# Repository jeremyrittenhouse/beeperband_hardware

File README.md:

This is the JITX-enabled beeper band design. 

The beeper design was started from a schematic but reworked using the JITX platform with the following features:
1) part discovery and bom generation
2) pin assignment for optimal connections between MCU and peripherals
3) adaptive, length-matched and differential trace implementation
4) semi-automatic power plane generation via voronoi region expansion

Note: to use the JITX platform, you will need to contact JITX for access to a beta version which enables some of the advanced features. (this note will go away when those features are in GA)

To run the code, open this repo in VSCode (w/JITX enabled) and load the file main.stanza. 
Press "Ctrl" + "Enter" in the file to run it. 

Please let me know if you have any questions. b.gupta@jitx.com

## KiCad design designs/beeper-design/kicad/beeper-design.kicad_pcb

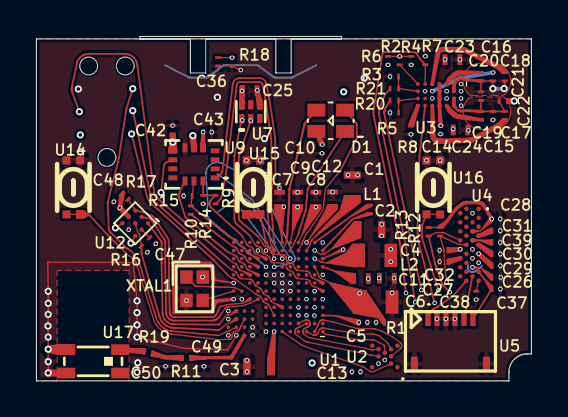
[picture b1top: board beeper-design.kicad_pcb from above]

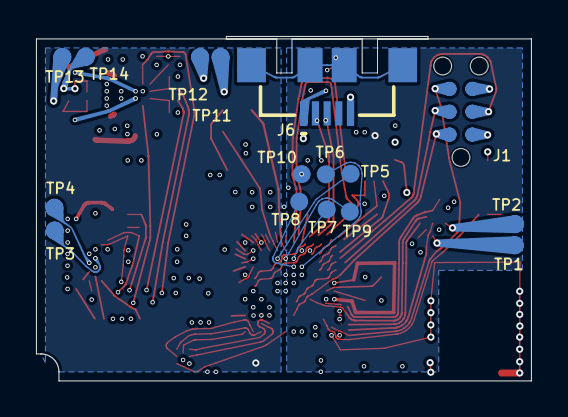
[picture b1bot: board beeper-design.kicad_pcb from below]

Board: 4 copper layers, 27.5 x 19.0 mm, 95 parts (16 on the bottom side), 87 nets.

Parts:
C1: 22u; Pkg0603_1
C2: 22u; Pkg0603_2
C3: 22u; Pkg0603
C4: 47u; Pkg0805
C5: 100n; Pkg0201_29
C6: 47u; Pkg0805_1
C7: 10u; Pkg0402_2
C8: 10u; Pkg0402_4
C9: 10u; Pkg0402_6
C10: 2.2u; Pkg0201_38
C11: 10u; Pkg0402_7
C12: 10u; Pkg0402
C13: 1u; Pkg0201
C14: 2.2u; Pkg0201_45
C15: 470n; Pkg0201_42
C16: 470n; Pkg0201_4
C17: 22n; Pkg0201_18
C18: 22n; Pkg0201_30
C19: 10n; Pkg0201_41
C20: 10n; Pkg0201_3
C21: 270p; Pkg0201_16
C22: 10n; Pkg0201_28
C23: 10u; Pkg0402_8
C24: 4.7u; Pkg0402_1
C25: 4.7u; Pkg0402_3
C26: 1u; Pkg0201_7
C27: 100n; Pkg0201_24
C28: 1u; Pkg0201_12
C29: 1u; Pkg0201_46
C30: 1u; Pkg0201_33
C31: 1u; Pkg0201_43
C32: 1u; Pkg0201_35
C36: 100n; Pkg0201_2
C37: 1u; Pkg0201_10
C38: 1u; Pkg0201_21
C39: 1u; Pkg0201_20
C42: 100n; Pkg0201_14
C43: 100n; Pkg0201_26
C47: 1u; Pkg0201_27
C48: 1u; Pkg0201_37
C49: 1p; Pkg0201_13
C50: 1p; Pkg0201_32
D1: LP_4
J1: TC2030_IDC_NL_FOOTPRINT
J6: GCT_USB3100_XX_X_REVB_1
L1: 470n; Pkg0201_11
L2: 1u; Pkg0402_5
R1: 0R; Pkg0201_47
R2: 845R; Pkg0201_9
R3: 10K; Pkg0201_6
R4: 20K; Pkg0201_34
R5: 10K; Pkg0201_44
R6: 196R; Pkg0201_23
R7: 10K; Pkg0201_19
R8: 1K; Pkg0201_31
R9: 0R; Pkg0201_8
R10: 0R; Pkg0201_17
R11: 0R; Pkg0201_22
R12, R13: 8K2; Pkg0201_1
R14, R15: 8K2; Pkg0201_36
R16, R17: 8K2; Pkg0201_5
R18: 100K; Pkg0201_40
R19: 0R; Pkg0201_39
R20: 0R; Pkg0201_15
R21: 0R; Pkg0201_25
TP1, TP2, TP3, TP4, TP5, TP6, TP7, TP8, TP9, TP10, TP11, TP12, TP13, TP14: SMD_TESTPT
U1: LP_7
U2: WLCSP_12
U3: LP_5
U4: LP_2
U5: LP_3
U7: SON_6_L1_5_W1_0_P0_50_BL
U9: LP
U12: LP_6
U14, U15, U16: LP_1
U17: Pkg_2450AT18D0100_STD_R_1
XTAL1: CRYSTAL_SMD_4P_L2_0_W1_6_BL_1

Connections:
AC1: C15.1, C17.1, C19.1, C21.2, C22.2, U3.B3, U3.B4
AC2: C16.1, C18.1, C20.1, C21.1, TP14.p, U3.B1, U3.B2
AD: R8.1, U3.G4
BOOT1: C19.2, U3.C4
BOOT2: C20.2, U3.C1
CLAMP1: C15.2, U3.E3
CLAMP2: C16.2, U3.E2
COMM1: C17.2, U3.E4
COMM2: C18.2, U3.E1
D+: J6.3, U1.F1, U7.1
D-: J6.2, U1.G1, U7.2
DACREF: C31.2, U4.A7
EN1: R5.1, R20.1, U3.G3
EN2: R3.1, R21.1, U3.G2
FOD: R2.2, R4.1, R6.1, U3.F2
GND: C1.1, C2.1, C3.1, C4.1, C5.1, C6.1, C7.1, C8.1, C9.1, C10.1, C11.1, C12.1, C13.1, C14.1, C23.1, C24.1, C25.1, C26.1, C27.1, C28.1, C29.1, C30.1, C31.1, C32.1, C36.2, C37.1, C38.1, C39.1, C42.1, C43.1, C47.1, C48.1, C49.2, C50.2, J1.5, J6.5, R3.2, R5.2, R6.2, R7.2, R8.2, R18.2, TP10.p, TP12.p, U1.A8, U1.A9, U1.A11, U1.A12, U1.B9, U1.C2, U1.C12, U1.D12, U1.E11, U1.E12, U1.F5, U1.F6, U1.G5, U1.G6, U1.G7, U1.G12, U1.H1, U1.H6, U1.H7, U1.H8, U1.L8, U1.L9, U1.M1, U2.C3, U3.A1, U3.A2, U3.A3, U3.A4, U4.B2, U4.B10, U5.2, U5.3, U5.4, U5.7, U5.8, U7.4, U9.7, U12.B3, U14.B, U14.B1, U15.B, U15.B1, U16.B, U16.B1, U17.2, U17.3, U17.4, XTAL1.2, XTAL1.4
ILIM: R2.1, U3.G1
LX: L1.1, U1.M2
LY: L1.2, U1.L1
LZ: L2.1, U1.J1
MICBIAS1: C37.2, U4.A15, U5.6
MICBIAS2: C38.2, U4.A17
OUT+: TP1.p, U12.A3
OUT-: TP2.p, U12.C3
RECT: C23.2, C24.2, R4.2, U3.C2, U3.C3
REG: C47.2, U12.A2
RF1: C49.1, R11.1, U1.A10
RF2: C50.1, R11.2, R19.1
RF3: R19.2, U17.1
SHIELD: C36.1, J6.6, J6.7, J6.8, J6.9, R18.1
SP_N: TP4.p, U4.A13
SP_P: TP3.p, U4.B12
V12: C1.2, U1.L3
V14RF: C2.2, C3.2, U1.A7, U1.L2
V18F: C5.2, C13.2, R1.1, U1.C1, U2.B2
VBAT: C8.2, TP11.p, U1.M4
VBUS: C9.2, C14.2, C25.2, J1.1, J6.1, U1.M5, U3.D1, U3.D2, U3.D3, U3.D4, U7.6
VDD1P8: C4.2, C42.2, C43.2, R14.2, R15.2, U1.K2, U9.5, U9.8
VDD1P8P: C6.2, C28.2, R1.2, R12.2, R13.2, U1.J2, U4.B6
VDD3P0: C7.2, C26.2, C32.2, U1.M6, U4.B14, U4.D10
VDDSYS: C11.2, C12.2, C29.2, C48.2, L2.2, R16.2, R17.2, U1.M3, U4.A11, U12.C2
VDIG: C27.2, U4.D12
VLED: C10.2, D1.2, U1.K1
VMID: C30.2, U4.A9
VREF: C39.2, U4.B8
XTAL32Mm: U1.F12, XTAL1.3
XTAL32Mp: U1.F11, XTAL1.1
board-io_rgb_b: D1.4, U1.L4
board-io_rgb_g: D1.3, U1.L6
board-io_rgb_r: D1.1, U1.L5
cap_p1: C22.1, TP13.p
codec-i2c-net_scl: R13.1, U1.C3, U4.D8
codec-i2c-net_sda: R12.1, U1.D4, U4.C9
codec-pdm-net_clk: U4.C17, U5.1
codec-pdm-net_data: U4.B16, U5.5
mcu_conn-uart_rx: J1.3, U1.H10
mcu_conn-uart_tx: J1.6, U1.B11
mcu_dbg-m33_swdio: J1.2, U1.C7
mcu_hap-gpio0_gpio: U1.D11, U12.A1
mcu_hap-gpio1_gpio: U1.E9, U12.B1
mcu_hap-i2c_scl: R17.1, U1.E10, U12.C1
mcu_hap-i2c_sda: R16.1, U1.C11, U12.B2
mcu_mcu-button0_gpio: U1.C10, U14.A, U14.A1
mcu_mcu-button1_gpio: U1.M8, U15.A, U15.A1
mcu_mcu-button2_gpio: U1.D2, U16.A, U16.A1
mcu_mcu-dbg-m33_swdclk: J1.4, U1.D6
mcu_mcu-etm_clk: TP5.p, U1.K5
mcu_mcu-etm_data0: TP6.p, U1.J8
mcu_mcu-etm_data1: TP7.p, U1.K7
mcu_mcu-etm_data2: TP8.p, U1.J7
mcu_mcu-etm_data3: TP9.p, U1.K6
mcu_mcu-mem_cs: U1.A6, U2.B4
mcu_mcu-mem_sck: U1.B4, U2.F2
mcu_mcu-mem_sdio0: U1.A1, U2.E3
mcu_mcu-mem_sdio1: U1.A2, U2.D4
mcu_mcu-mem_sdio2: U1.A3, U2.F4
mcu_mcu-mem_sdio3: U1.B3, U2.D2
mcu_mcu-wpwr0_gpio: R20.2, U1.E3
mcu_mcu-wpwr1_gpio: R21.2, U1.E1
mcu_mcu-wpwr2_gpio: U1.C4, U3.F4
mcu_mcu-wpwr3_gpio: R7.1, U1.F2, U3.F1
mcu_q-i3c_scl: R10.1, R15.1, U1.K9, U9.13
mcu_q-i3c_sda: R9.1, R14.1, U1.K8, U9.14
mcu_q-spi_cs: U1.H9, U9.12
mcu_q-spi_sck: R10.2, U1.J9
mcu_q-spi_sdi: U1.M7, U9.1
mcu_q-spi_sdo: R9.2, U1.L7

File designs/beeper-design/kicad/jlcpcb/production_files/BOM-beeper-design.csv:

Comment,Designator,Footprint,LCSC
0R,R1,Pkg0201_18,C106228
BQ51003YFPR,U3,LP_7,C134093
EVPBB4A9B000,"U14,U15,U16",LP_2,C140848
AT25FF321A-UUN-T,U2,WLCSP_12,C1858339
CSD75207W15,U13,LP_6,C201968
DA7212-01UM2,U4,LP_3,C2649370
~,U17,Pkg_2450AT18D0100_STD_R_1,C2917718
23-23B/R6GHBHW-C30/2A,U6,LP_4,C2922368
TPD4S012DRYR,U7,SON_6_L1_5_W1_0_P0_50_BL,C2959843
FH19C-6S-0.5SH(10),U5,LP_5,C424651
LSM6DSOXTR,U9,LP_1,C481766
100n,"C27,C36,C42,C43,C5",Pkg0201_44,C76934
1u,"C13,C26,C28,C29,C30,C31,C32,C33,C34,C35,C37,C38,C39,C47,C48",Pkg0201_27,C76935
DRV2605YZFR,U12,LP_8,C81079
XRCGB32M000F1H00R0,XTAL1,CRYSTAL_SMD_4P_L2_0_W1_6_BL_1,C880116
1n,L3,Pkg0201_40,
1n,L4,Pkg0201_9,
1p,C49,Pkg0201_32,
1p,C50,Pkg0201_2,
10u,C12,Pkg0402,
470n,L1,Pkg0603_3,
1u,L2,Pkg0402_7,
10u,C11,Pkg0402_1,
DA14705-00000HZ2,U1,LP,
10103594-0001LF,J6,AMPHENOL_10103594_0001LF,
100K,R18,Pkg0201_13,
8K2,R15,Pkg0201_5,
22u,C3,Pkg0603_2,
22u,C2,Pkg0603_1,
8K2,R14,Pkg0201_5,
22u,C1,Pkg0603,
8K2,R13,Pkg0201_20,
10K,R7,Pkg0201_16,
10K,R5,Pkg0201_39,
10K,R6,Pkg0201_4,
1K,R8,Pkg0201_28,
8K2,R12,Pkg0201_20,
470n,C15,Pkg0402_5,
22n,C18,Pkg0201_26,
470n,C16,Pkg0402_10,
22n,C17,Pkg0201_14,
10n,C20,Pkg0201_45,
270p,C21,Pkg0201_12,
8K2,R16,Pkg0201_30,
10n,C19,Pkg0201_36,
8K2,R17,Pkg0201_30,
4.7u,C24,Pkg0402_8,
20K,R4,Pkg0201_29,
10u,C9,Pkg0402_9,
196R,R3,Pkg0201_17,
845R,R2,Pkg0201_6,
2.2u,C14,Pkg0201_41,
2.2u,C10,Pkg0201_11,
10n,C22,Pkg0201_23,
10u,C23,Pkg0402_3,
47u,C6,Pkg0805,
47u,C4,Pkg0805_1,
10u,C7,Pkg0402_2,
10u,C8,Pkg0402_4,
4.7u,C25,Pkg0402_6,

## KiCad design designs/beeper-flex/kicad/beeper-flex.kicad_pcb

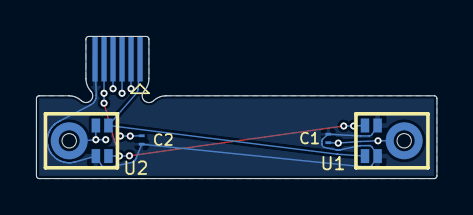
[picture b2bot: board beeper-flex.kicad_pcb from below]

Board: 2 copper layers, 22.2 x 7.9 mm, 5 parts (5 on the bottom side), 4 nets.

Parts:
C1, C2: 100n; Pkg0201
U1, U2: LP
U3: EDGE_LP

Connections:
GND: C1.1, C2.1, U1.5, U2.4, U2.5, U3.2, U3.3, U3.4
PDM_clk: U1.3, U2.3, U3.1
PDM_data: U1.1, U2.1, U3.5
VDDMIC: C1.2, C2.2, U1.2, U1.4, U2.2, U3.6

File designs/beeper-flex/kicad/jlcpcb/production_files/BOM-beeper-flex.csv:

Comment,Designator,Footprint,LCSC
~,U2,LP,
~,U1,LP,
100n,C2,Pkg0201,
100n,C1,Pkg0201,

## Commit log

2023-10-07 initial checkin for beeper design
2023-10-07 add a README.md
2023-10-07 make ctrl enter show up
2023-10-07 better terminology
2023-10-07 added 3D models
2023-10-07 improved schematic layout a bit
2023-10-10 improved footprint of DA14705
2023-10-10 fixed orientation of DA14705
2023-10-10 changed xtal, esd
2023-10-10 cached part
2023-10-10 check in of unplaced design on top
2023-10-10 oops some extra files to check-in
2023-10-10 fixed up schematic a little bit
2023-10-10 some minor layout changes (usb conn moved off-board)
2023-10-10 updated gitignore
2023-10-11 updated debug
2023-10-11 fixed BGA ball landpattern
2023-10-11 starting to do some power routing
2023-10-12 interim check-in for debugging
2023-10-16 design check-in with better schematics, layout options
2023-10-16 tweaking schematic
2023-10-16 tweaking schematic a bit more
2023-10-16 changed name of micro
2023-10-17 testing schematic stability
2023-10-17 changed page size for export to match notmal size
2023-10-18 store current state for demo
2023-10-20 adding prelim flex design
2023-10-20 move broken
2023-10-20 removed extra point
2023-10-20 interim check-in for flex placement
2023-10-23 added more to the flex, connector
2023-10-24 reorganized mcu supports, fixed leds
2023-10-24 check in for code placed movement
2023-10-25 stage check-in for pre-updating jitx-client
2023-10-27 in the midst of restructuring the code, check-in
2023-10-27 updated ignored file
2023-10-27 intro'ed top level bundles and board-io module
2023-10-27 checkpoint for debugging crash
2023-10-28 checkpoint for partial crash soln
2023-10-30 checkpoint with new CustomLayer defn
2023-10-30 checkpoint running without board
2023-10-31 fixed CustomLayer display -- design ok
2023-10-31 design now not ok, hmmm
2023-10-31 commit good version with CustomLayer having sides
2023-11-03 fixed paste mask on BGA pads
2023-11-03 convenient check-in for realization issue
2023-11-07 updated design with led/speaker + 6p flex
2023-11-07 moved cmps
2023-11-14 latest checkpoint with newer ocdb + vias
2023-11-14 missing via?
2023-11-15 export-desing() not working
2023-11-16 flex design stable-ish on si-branch
2023-11-16 vdd pour not rendering
2023-11-16 vdd pour not rendering upon deleting extra gnd vias
2023-11-17 somewhat stable flex design
2023-11-17 pin assigment issue??
2023-11-17 experimenting with removing requires/supports
2023-11-17 ok kicad version
2023-11-18 reverted version
2023-11-18 updated with stuff from broken main
2023-11-18 further refined older design (develop)
2023-11-18 changed polylines to lines for BoardEdge()
2023-11-18 updated export from kicad
2023-11-18 new file for kicad
2023-11-20 improved cutout/soldermas for mics
2023-11-20 improved exported design
2023-11-21 added bom + new disti
2023-11-21 new flex board outline
2023-11-21 reduced stiffener
2023-11-21 added another vdd strap in flex
2023-11-21 bom for flex
2023-11-22 added 3d model + fixed directory
2023-11-22 refactored top level, added one step file
2023-11-22 fixed up 3D flex conn
2023-11-25 better export + JLCPCB numbers
2023-11-25 misc sch
2023-12-05 added 1 microvia
2023-12-07 updated LED
2023-12-07 checkin physical cache
2023-12-11 checkpoint on via crash
2023-12-12 flex connector not placed correctly
2023-12-12 schematic issue 14:35
2023-12-12 auto-via not selecting correct via
2023-12-20 removed extra caps, organizing sch
2023-12-22 almost routed
2023-12-22 initial routing done
2023-12-23 refined layout connectivity
2023-12-23 reran, no schematic generated
2023-12-24 deleted old crashy schematic
2023-12-25 updating schematic
2023-12-25 updating schematic again
2024-01-02 incrementally improving schematic
2024-01-03 post export, had to munge sch
2024-01-05 schematic edit check-in
2024-01-08 fixed up schematic a bit more
2024-01-08 just did a reload in the REPL with a submodule move in the sch
2024-01-09 fixing drc errors
2024-01-09 moving submodules in sch
2024-01-09 updated kicad export
2024-01-09 better schematic
2024-01-09 exported yet again
2024-01-09 exported yet again 2
2024-01-10 updated schematic and layout for vias
2024-01-10 made ocdb a submodule
2024-01-10 some minor sch changes
2024-01-10 use dev version of ocdb
2024-01-11 optimizing BOM
2024-01-11 updated this branch to match old main-new
2024-01-11 one more line to match old main-new
2024-01-12 kicad exported data
2024-01-12 added flex data
2024-01-12 some random sch changes?
2024-01-12 added flex kicad export
2024-01-12 made flex edge conn to NotInBOM
2024-01-12 update flex BOM
2024-01-12 flex to cad with wrong rules
2024-01-12 fixed flex kicad project and exported for JLCPCB
2024-01-12 added zip file of gerbers
2024-01-13 schematic keeps updating itself -- forcing new user edits
2024-01-14 rejiggered power supplies
2024-01-15 did all fixes per feedback
2024-01-15 updated per latest power scheme
2024-01-15 layout ok
2024-01-15 debug on, optimize layout, sch crash
2024-01-15 saved phy layout
2024-01-16 tried some sch opt
2024-01-16 export broken, move tps broken
2024-01-16 fixed more layout, optimized vias
2024-01-16 improving schematic again
2024-01-16 crashing on via deletion
2024-01-17 another export
2024-01-17 crash with new usb connector
2024-01-17 some more complete files for the crash
2024-01-17 saved after a lot of layout optimization
2024-01-17 removing jitx_* debug files
2024-01-17 disabled enable-spy()
2024-01-17 new export
2024-01-17 unrealizable route?
2024-01-17 optimized vdd3p0
2024-01-17 reasonble export
2024-01-17 cleaned up kicad export files
2024-01-18 added newer BOM files
2024-01-19 Special via
2024-01-19 Pours?
2024-01-23 debugging max-clearance
2024-01-26 Pour graph error
2024-01-26 Failing on graph thing
2024-01-29 Pours working again.
2024-01-29 Fixed pours
2024-01-29 Finalized pours
2024-01-29 moving haptic
2024-01-30 Added length matching, removed pours
2024-01-31 flex redo with looser rules
2024-02-01 saved design - duh
2024-02-01 crashing on main, flex ok-ish
2024-02-02 updated flex with export
2024-02-02 updated designators:
2024-02-02 fixed up kicad for flex
2024-02-02 updated gerbers for flex
2024-02-02 one last kicad state file
2024-02-05 Drag realization error
2024-02-05 final design?
2024-02-05 Work around issue in topology engine
2024-02-10 moved antenna, fixed??? routing
2024-02-10 exported, yet XTALM32p keeps disappearing
2024-02-12 fixed up pours, keepout regions
2024-02-13 exported to Kicad, fixed Kicad, exported gerbers
2024-02-13 generated design zip + pos
2024-02-14 fixed typo in stackup name
2024-02-21 checkpoint on beeper 2-21
2024-02-21 updated some constraints
2024-02-22 latest fully routed version
